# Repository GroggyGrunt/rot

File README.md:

# rot - synthcircuits
easygoing eurorack-modules 

## takt - devided trigger generator

#### takt-ex - expander 

## rør - active multiple

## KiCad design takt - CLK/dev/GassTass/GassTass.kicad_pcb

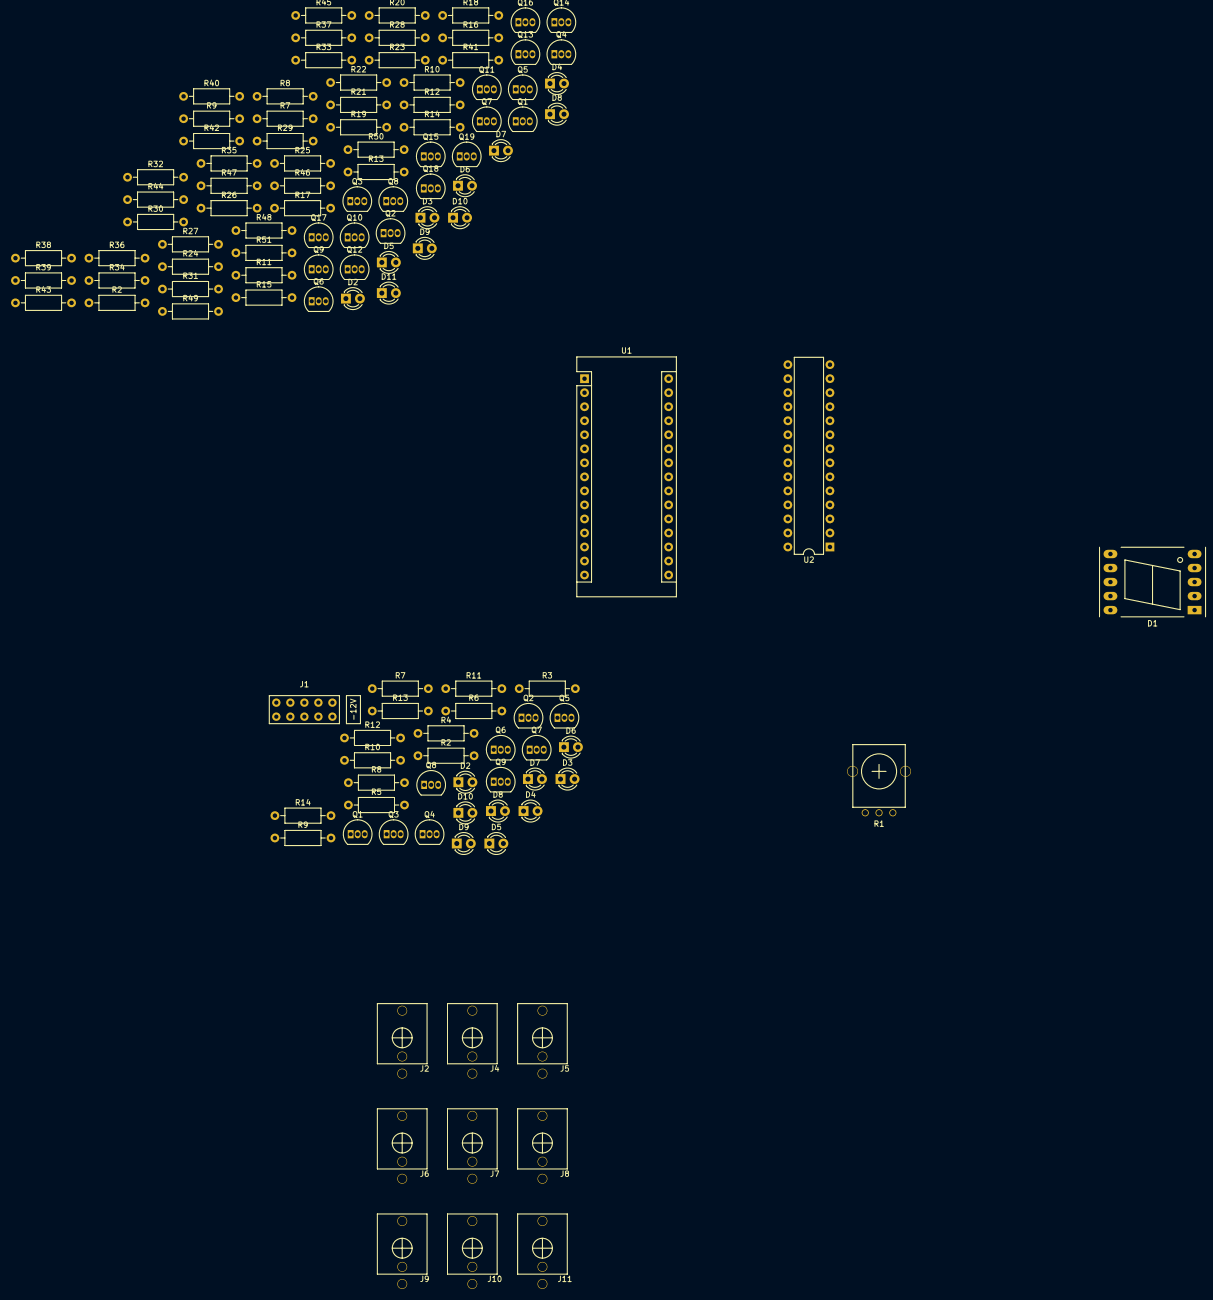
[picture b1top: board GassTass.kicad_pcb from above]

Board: 2 copper layers, 120 parts (0 on the bottom side), 87 nets, no tracks yet.

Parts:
D1: CC56-12CGKWA; 7SegmentLED_LTS6760_LTS6780
D2, D2#2, D3, D3#2, D4, D4#2, D5, D5#2, D6, D6#2, D7, D7#2, D8, D8#2, D9, D9#2, D10, D10#2, D11: LED; LED_D3.0mm_FlatTop
J1: EURO_PWR_2x5; europwr2x5
J2, J4, J5, J6, J7, J8, J9, J10, J11: PJ301M-12
Q1, Q1#2, Q2, Q2#2, Q3, Q3#2, Q4, Q4#2, Q5, Q5#2, Q6, Q6#2, Q7, Q7#2, Q8, Q8#2, Q9, Q9#2, Q10, Q11, Q12, Q13, Q14, Q15, Q16, Q17, Q18, Q19: 2N3904; TO-92_Inline
R1: R_POT_US; Alpha9mmPot
R2, R11, R17, R22, R27, R32, R37, R42, R47: 200; R_Axial_DIN0207_L6.3mm_D2.5mm_P10.16mm_Horizontal
R2#2, R3, R4, R5, R6, R7#2, R8#2, R9#2, R10#2, R11#2, R12#2, R13, R13#2, R14#2: R_US; R_Axial_DIN0207_L6.3mm_D2.5mm_P10.16mm_Horizontal
R7, R9, R10, R12, R15, R16, R18, R20, R21, R23, R25, R26, R28, R30, R31, R33, R35, R36, R38, R40, R41, R43, R45, R46, R48, R50, R51: 1k; R_Axial_DIN0207_L6.3mm_D2.5mm_P10.16mm_Horizontal
R8, R14, R19, R24, R29, R34, R39, R44, R49: 10k; R_Axial_DIN0207_L6.3mm_D2.5mm_P10.16mm_Horizontal
U1: Arduino_Nano_v3.x; Arduino_Nano
U2: ATmega328P-PU; DIP-28_W7.62mm

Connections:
+5V: R8.1, R14.1, R19.1, R24.1, R29.1, R34.1, R39.1, R44.1, R49.1
+12V: J1.1, J1.2, Q1#2.3, Q2#2.3, Q3#2.3, Q4#2.3, Q5.3, Q5#2.3, Q6#2.3, Q7#2.3, Q8#2.3, Q9#2.3, R10.1, R16.1, R21.1, R26.1, R31.1, R36.1, R41.1, R46.1, R51.1
-12V: J1.9, J1.10
GND: D2.1, D3.1, D5.1, D6.1, D7.1, D8.1, D9.1, D10.1, D11.1, J1.3, J1.4, J1.5, J1.6, J1.7, J1.8, J2.1, J2.2, J4.1, J4.2, J5.1, J5.2, J6.1, J6.2, J7.1, J7.2, J8.1, J8.2, J9.1, J9.2, J10.1, J10.2, J11.1, J11.2, Q1.1, Q2.1, Q3.1, Q4.1, Q6.1, Q7.1, Q8.1, Q9.1, Q10.1, Q11.1, Q12.1, Q13.1, Q14.1, Q15.1, Q16.1, Q17.1, Q18.1, Q19.1, R1.1, R2#2.1, R7#2.1, R8#2.1, R9#2.1, R10#2.1, R11#2.1, R12#2.1, R13.1, R13#2.1, R14#2.1, U1.4, U1.29, U2.8, U2.22
unnamed: D1.1, U2.16
unnamed: D1.2, U2.15
unnamed: D1.4, U2.14
unnamed: D1.5, U2.18
unnamed: D1.6, R3.1
unnamed: D1.7, U2.13
unnamed: D1.8, R4.1
unnamed: D1.9, R5.1
unnamed: D1.10, U2.17
unnamed: D2#2.1, R2#2.2
unnamed: D2.2, D2#2.2, Q1#2.2, R2.2
unnamed: D3#2.1, R7#2.2
unnamed: D3.2, D3#2.2, Q2#2.2, R11.2
unnamed: D4.1, D4#2.1, R8#2.2, R13.2
unnamed: D4.2, D4#2.2, Q3#2.2, Q5.2
unnamed: D5#2.1, R9#2.2
unnamed: D5.2, D5#2.2, Q4#2.2, R17.2
unnamed: D6#2.1, R10#2.2
unnamed: D6.2, D6#2.2, Q5#2.2, R22.2
unnamed: D7#2.1, R11#2.2
unnamed: D7.2, D7#2.2, Q6#2.2, R27.2
unnamed: D8#2.1, R12#2.2
unnamed: D8.2, D8#2.2, Q7#2.2, R32.2
unnamed: D9#2.1, R13#2.2
unnamed: D9.2, D9#2.2, Q8#2.2, R37.2
unnamed: D10#2.1, R14#2.2
unnamed: D10.2, D10#2.2, Q9#2.2, R42.2
unnamed: D11.2, R47.2
unnamed: J2.3, Q1#2.1, Q2.3, R10.2
unnamed: Q2#2.1, Q5.1
unnamed: J4.3, Q3#2.1, Q4.3, R16.2
unnamed: J5.3, Q4#2.1, Q7.3, R21.2
unnamed: J6.3, Q5#2.1, Q9.3, R26.2
unnamed: J7.3, Q6#2.1, Q11.3, R31.2
unnamed: J8.3, Q7#2.1, Q13.3, R36.2
unnamed: J9.3, Q8#2.1, Q15.3, R41.2
unnamed: J10.3, Q9#2.1, Q17.3, R46.2
unnamed: J11.3, Q19.3, R51.2
unnamed: Q1.2, R7.2
unnamed: Q1.3, R8.2, R9.2
unnamed: Q2.2, R9.1
unnamed: Q3.2, R12.2
unnamed: Q3.3, R14.2, R15.2
unnamed: Q4.2, R15.1
unnamed: Q6.2, R18.2
unnamed: Q6.3, R19.2, R20.2
unnamed: Q7.2, R20.1
unnamed: Q8.2, R23.2
unnamed: Q8.3, R24.2, R25.2
unnamed: Q9.2, R25.1
unnamed: Q10.2, R28.2
unnamed: Q10.3, R29.2, R30.2
unnamed: Q11.2, R30.1
unnamed: Q12.2, R33.2
unnamed: Q12.3, R34.2, R35.2
unnamed: Q13.2, R35.1
unnamed: Q14.2, R38.2
unnamed: Q14.3, R39.2, R40.2
unnamed: Q15.2, R40.1
unnamed: Q16.2, R43.2
unnamed: Q16.3, R44.2, R45.2
unnamed: Q17.2, R45.1
unnamed: Q18.2, R48.2
unnamed: Q18.3, R49.2, R50.2
unnamed: Q19.2, R50.1
unnamed: R1.2, U1.19
unnamed: R1.3, U1.18
unnamed: R3.2, U2.4
unnamed: R4.2, U2.5
unnamed: R5.2, U2.6
unnamed: R6.2, U2.11
unnamed: U1.23, U2.27
unnamed: U1.24, U2.28
unnamed: U1.27, U2.7
Tr1-in: R2.1, R7.1, U1.5
Tr2-in: R11.1, R12.1, U1.6
Tr3-in: R17.1, R18.1, U1.7
Tr4-in: R22.1, R23.1, U1.8
Tr5-in: R27.1, R28.1, U1.9
Tr6-in: R32.1, R33.1, U1.10
Tr7-in: R37.1, R38.1, U1.11
Tr8-in: R42.1, R43.1, U1.12
Tr9-in: R47.1, R48.1, U1.13

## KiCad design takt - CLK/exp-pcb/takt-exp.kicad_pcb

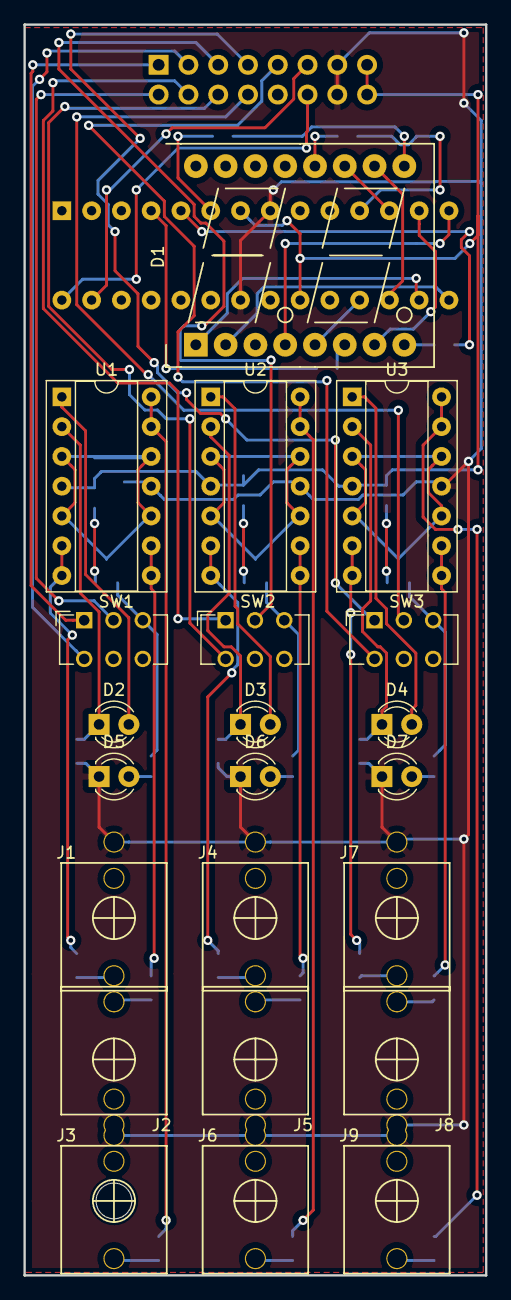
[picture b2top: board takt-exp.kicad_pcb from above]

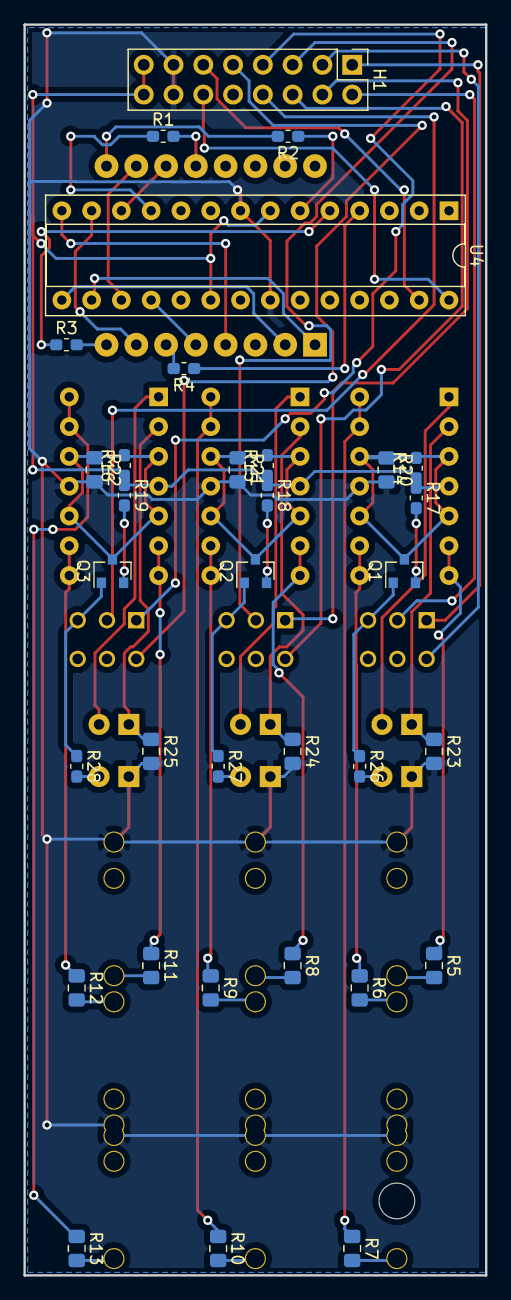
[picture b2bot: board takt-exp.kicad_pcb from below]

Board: 2 copper layers, 39.4 x 106.7 mm, 55 parts (33 on the bottom side), 64 nets.

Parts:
D1: CC56-12CGKWA; AFF_2x7SEG-DIGIT_10mm
D2, D3, D4, D5, D6, D7: LED; LED_D3.0mm_FlatTop
H1: Expander; PinHeader_2x08_P2.54mm_Vertical
J1, J2, J3, J4, J5, J6, J7, J8, J9: PJ301M-12
Q1, Q2, Q3: 2N3904; SOT-23
R1, R2, R3, R4, R26, R27, R28: 200; R_0603_1608Metric_Pad1.05x0.95mm_HandSolder
R5, R6, R7, R8, R9, R10, R11, R12, R13: 51; R_0805_2012Metric_Pad1.15x1.40mm_HandSolder
R14, R15, R16: 6.8k; R_0603_1608Metric_Pad1.05x0.95mm_HandSolder
R17, R18, R19: 2.2k; R_0603_1608Metric_Pad1.05x0.95mm_HandSolder
R20, R21, R22: 10m; R_0805_2012Metric_Pad1.15x1.40mm_HandSolder
R23, R24, R25: 1k; R_0805_2012Metric_Pad1.15x1.40mm_HandSolder
SW1, SW2, SW3: SW_SP3T; SW_CuK_JS202011CQN_DPDT_Straight
U1, U2, U3: TL074; DIP-14_W7.62mm_Socket
U4: ATmega328P-PU; DIP-28_W7.62mm_Socket

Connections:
5V: H1.15, H1.16, R14.1, R15.1, R16.1, R17.1, R18.1, R19.1, U1.4, U2.4, U3.4, U4.7, U4.20
C1: R1.1, U4.11
C2: R2.1, U4.6
C3: R3.1, U4.5
C4: R4.1, U4.4
GND: D5.1, D6.1, D7.1, H1.13, H1.14, J1.1, J2.1, J3.1, J4.1, J5.1, J6.1, J7.1, J8.1, J9.1, R20.2, R21.2, R22.2, R23.2, R24.2, R25.2, U1.11, U2.11, U3.11, U4.8, U4.22
La: D1.11, U4.12
Lb: D1.7, U4.13
Lc: D1.4, U4.14
Ld: D1.2, U4.15
Le: D1.1, U4.16
Lf: D1.10, U4.17
Lg: D1.5, U4.18
unnamed: D1.6, R4.2
unnamed: D1.8, R3.2
unnamed: D1.9, R2.2
unnamed: D1.12, R1.2
unnamed: D2.1, R23.1, U1.2
unnamed: D2.2, U1.1
unnamed: D3.1, R24.1, U2.2
unnamed: D3.2, U2.1
unnamed: D4.1, R25.1, U3.2
unnamed: D4.2, U3.1
unnamed: D5.2, R26.2
unnamed: D6.2, R27.2
unnamed: D7.2, R28.2
unnamed: J1.3, R5.2
unnamed: J2.3, R6.2
unnamed: J3.3, R7.2
unnamed: J4.3, R8.2
unnamed: J5.3, R9.2
unnamed: J6.3, R10.2
unnamed: J7.3, R11.2
unnamed: J8.3, R12.2
unnamed: J9.3, R13.2
unnamed: Q1.2, R17.2
unnamed: Q1.3, R14.2, R20.1, U1.3, U1.5, U1.10, U1.12
unnamed: Q2.2, R18.2
unnamed: Q2.3, R15.2, R21.1, U2.3, U2.5, U2.10, U2.12
unnamed: Q3.2, R19.2
unnamed: Q3.3, R16.2, R22.1, U3.3, U3.5, U3.10, U3.12
unnamed: R5.1, U1.6, U1.7
unnamed: R6.1, U1.8, U1.9
unnamed: R7.1, U1.13, U1.14
unnamed: R8.1, U2.6, U2.7
unnamed: R9.1, U2.8, U2.9
unnamed: R10.1, U2.13, U2.14
unnamed: R11.1, U3.6, U3.7
unnamed: R12.1, U3.8, U3.9
unnamed: R13.1, U3.13, U3.14
SDA: H1.11, U4.27
SDC: H1.12, U4.28
Tr1: H1.1, SW1.1
Tr2: H1.2, SW1.2
Tr3: H1.3, SW1.4
Tr4: H1.4, SW2.1
Tr5: H1.5, SW2.2
Tr6: H1.6, SW2.4
Tr7: H1.7, SW3.1
Tr8: H1.8, SW3.2
Tr9: H1.9, SW3.4
sw1: Q1.1, R26.1, SW1.3
sw2: Q2.1, R27.1, SW2.3
sw3: Q3.1, R28.1, SW3.3

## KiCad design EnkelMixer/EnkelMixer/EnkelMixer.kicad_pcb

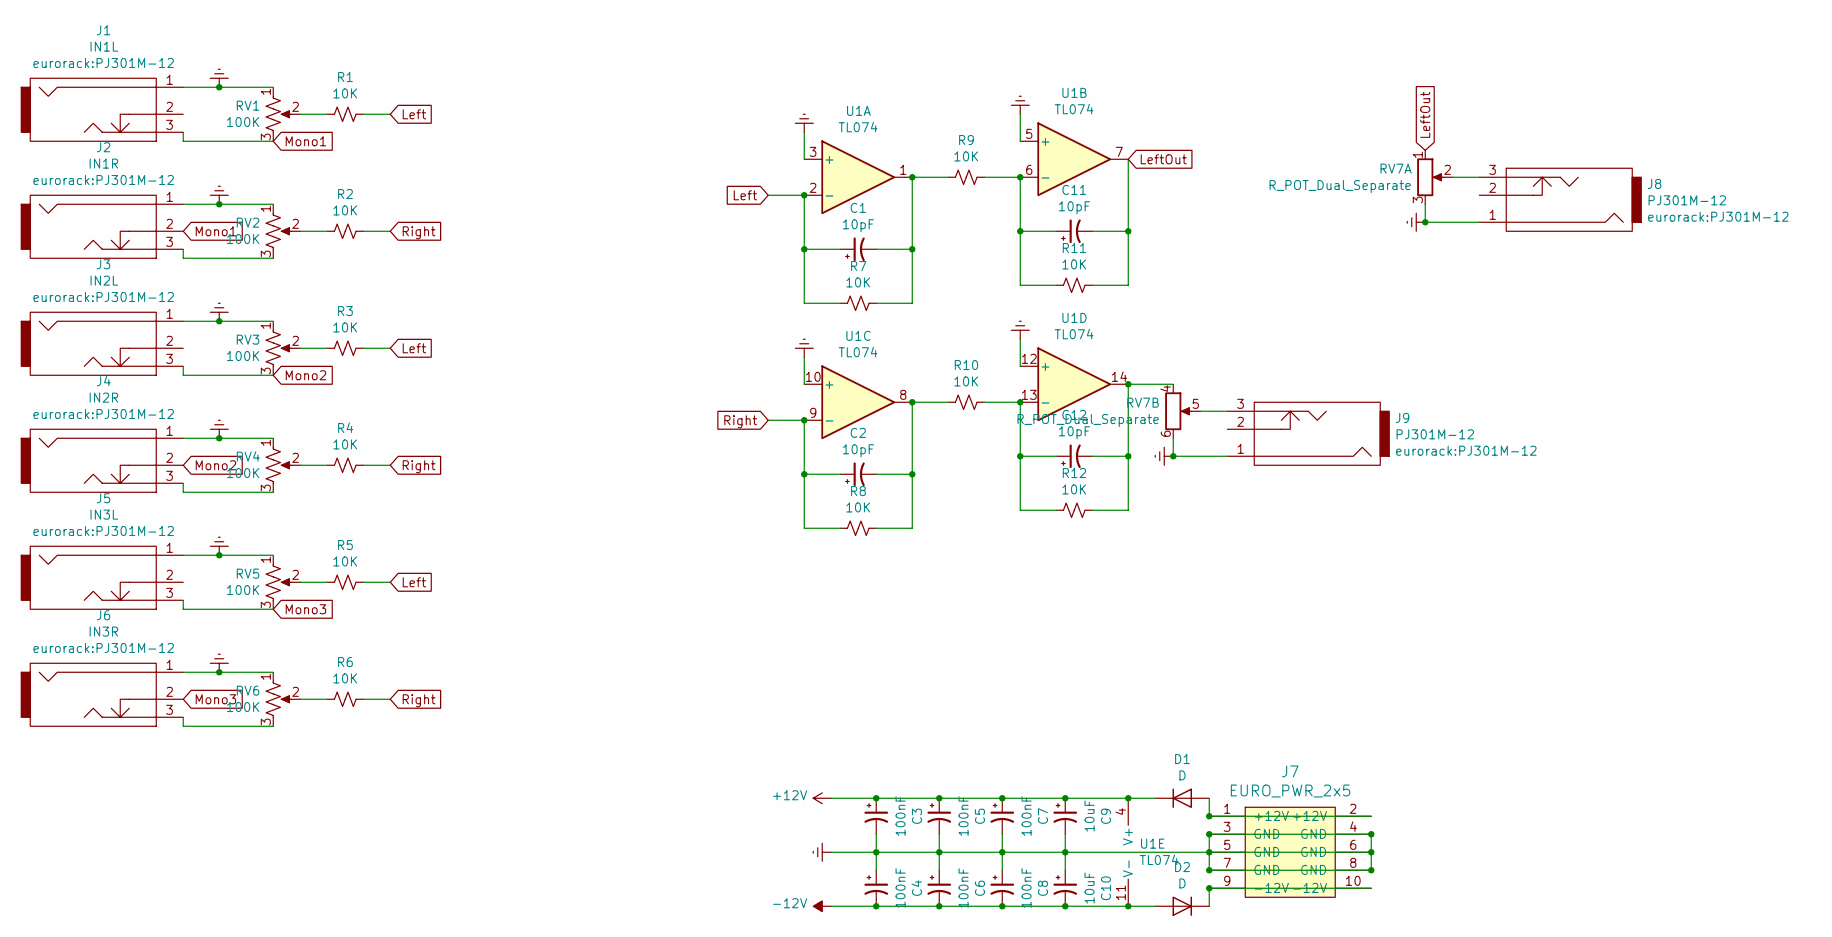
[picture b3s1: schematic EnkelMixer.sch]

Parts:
C1, C2, C11, C12: 10pF; C_Disc_D5.0mm_W2.5mm_P5.00mm
C3, C4, C5, C6, C7, C8: 100nF; C_Disc_D5.0mm_W2.5mm_P5.00mm
C9, C10: 10uF; C_Disc_D5.0mm_W2.5mm_P5.00mm
D1, D2: D; D_A-405_P7.62mm_Horizontal
J1: IN1L; PJ301M-12
J2: IN1R; PJ301M-12
J3: IN2L; PJ301M-12
J4: IN2R; PJ301M-12
J5: IN3L; PJ301M-12
J6: IN3R; PJ301M-12
J7: EURO_PWR_2x5; PinHeader_2x05_P2.54mm_Vertical
J8, J9: PJ301M-12
R1, R2, R3, R4, R5, R6, R7, R8, R9, R10, R11, R12: 10K; R_Axial_DIN0207_L6.3mm_D2.5mm_P5.08mm_Vertical
RV1, RV2, RV3, RV4, RV5, RV6: 100K; Potentiometer_Alpha_RD901F-40-00D_Single_Vertical
RV7: R_POT_Dual_Separate; Potentiometer_Alpha_RD902F-40-00D_Dual_Vertical
U1: TL074; DIP-14_W7.62mm_LongPads

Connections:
+12V: C3.1, C5.1, C7.1, C9.1, D1.1 (K), U1.4 (V+)
-12V: C4.2, C6.2, C8.2, C10.2, D2.2 (A), U1.11 (V-)
Earth: C3.2, C4.1, C5.2, C6.1, C7.2, C8.1, C9.2, C10.1, J1.1, J2.1, J3.1, J4.1, J5.1, J6.1, J7.3 (GND), J7.4 (GND), J7.5 (GND), J7.6 (GND), J7.7 (GND), J7.8 (GND), J8.1, J9.1, RV1.1, RV2.1, RV3.1, RV4.1, RV5.1, RV6.1, RV7.3, RV7.6, U1.3 (+), U1.5 (+), U1.10 (+), U1.12 (+)
Left: C1.1, R1.1, R3.1, R5.1, R7.2, U1.2 (-)
Mono1: J1.3, J2.2, RV1.3
Mono2: J3.3, J4.2, RV3.3
Mono3: J5.3, J6.2, RV5.3
unnamed: C1.2, R7.1, R9.2, U1.1
unnamed: C2.2, R8.1, R10.2, U1.8
unnamed: C11.1, R9.1, R11.2, U1.6 (-)
unnamed: C11.2, R11.1, RV7.1, U1.7
unnamed: C12.1, R10.1, R12.2, U1.13 (-)
unnamed: C12.2, R12.1, RV7.4, U1.14
unnamed: D1.2 (A), J7.1 (+12V), J7.2 (+12V)
unnamed: D2.1 (K), J7.9 (-12V), J7.10 (-12V)
unnamed: J2.3, RV2.3
unnamed: J4.3, RV4.3
unnamed: J6.3, RV6.3
unnamed: J8.3, RV7.2
unnamed: J9.3, RV7.5
unnamed: R1.2, RV1.2
unnamed: R2.2, RV2.2
unnamed: R3.2, RV3.2
unnamed: R4.2, RV4.2
unnamed: R5.2, RV5.2
unnamed: R6.2, RV6.2
Right: C2.1, R2.1, R4.1, R6.1, R8.2, U1.9 (-)

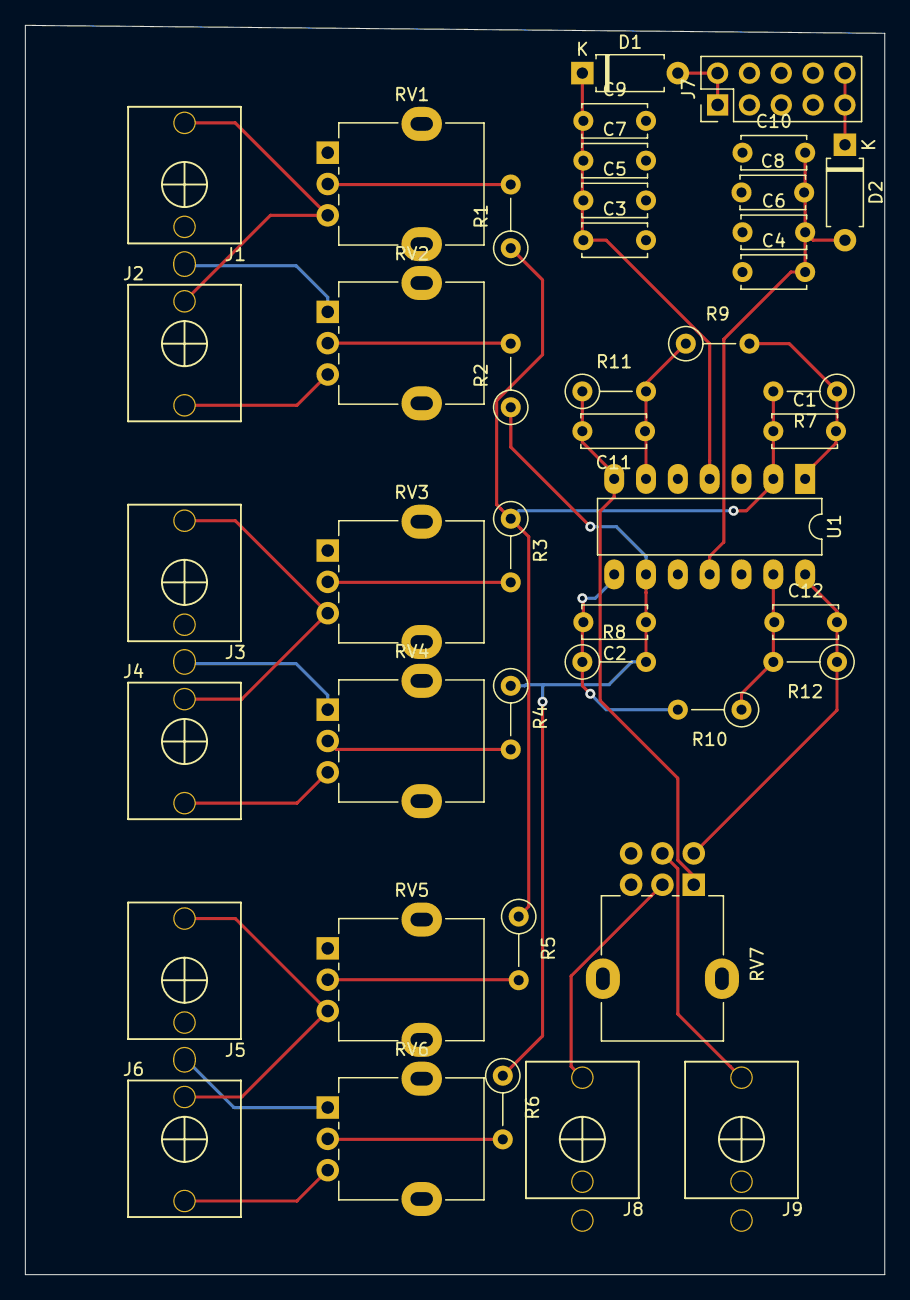
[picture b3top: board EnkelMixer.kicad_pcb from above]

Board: 2 copper layers, 68.6 x 99.7 mm, 43 parts (0 on the bottom side), 27 nets.

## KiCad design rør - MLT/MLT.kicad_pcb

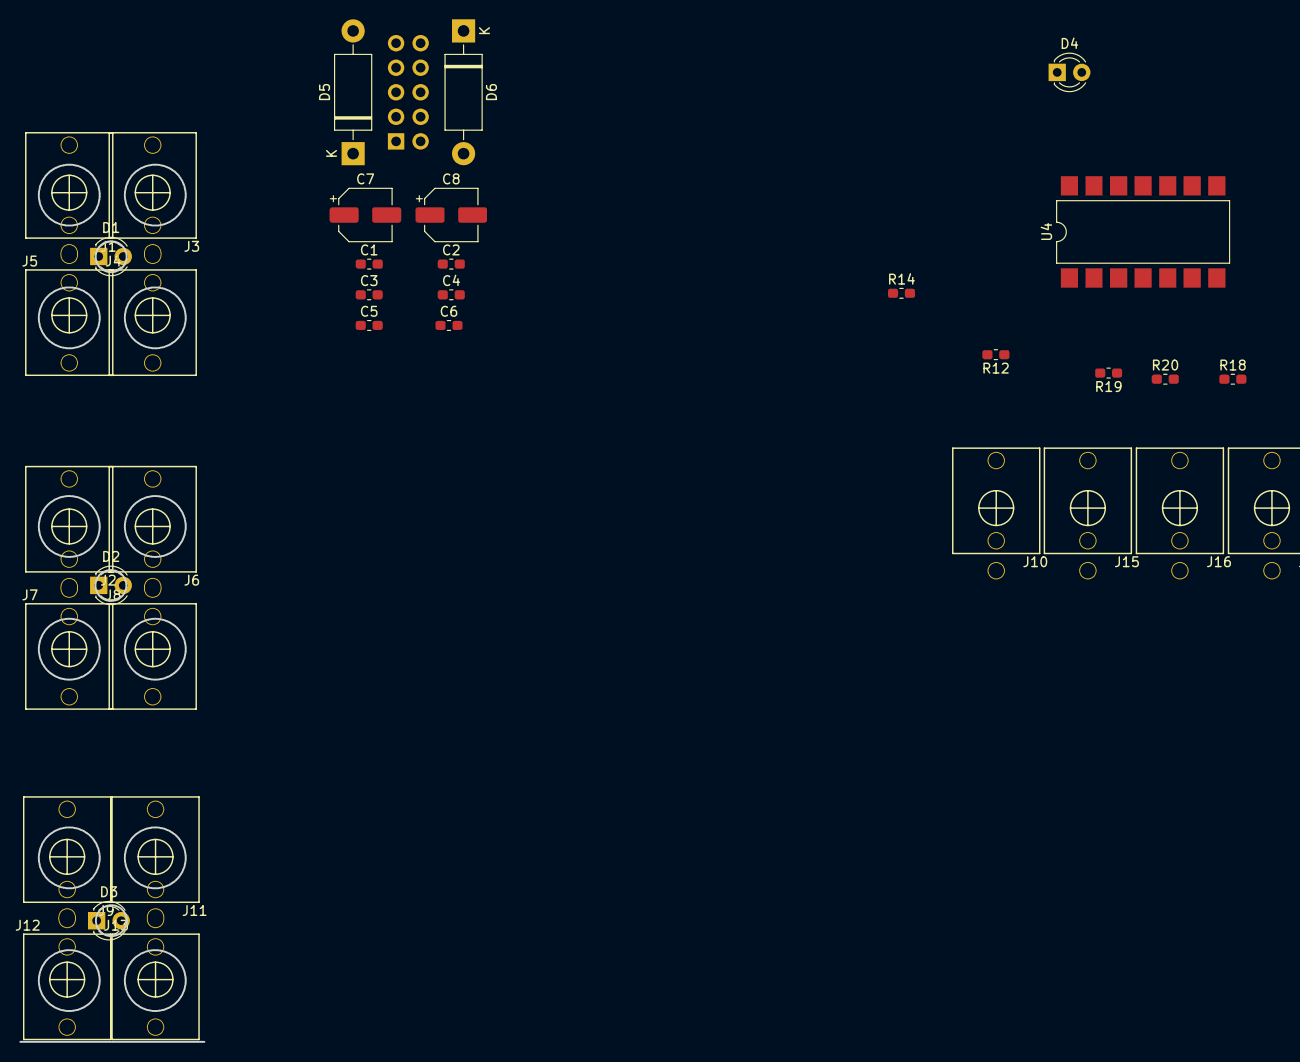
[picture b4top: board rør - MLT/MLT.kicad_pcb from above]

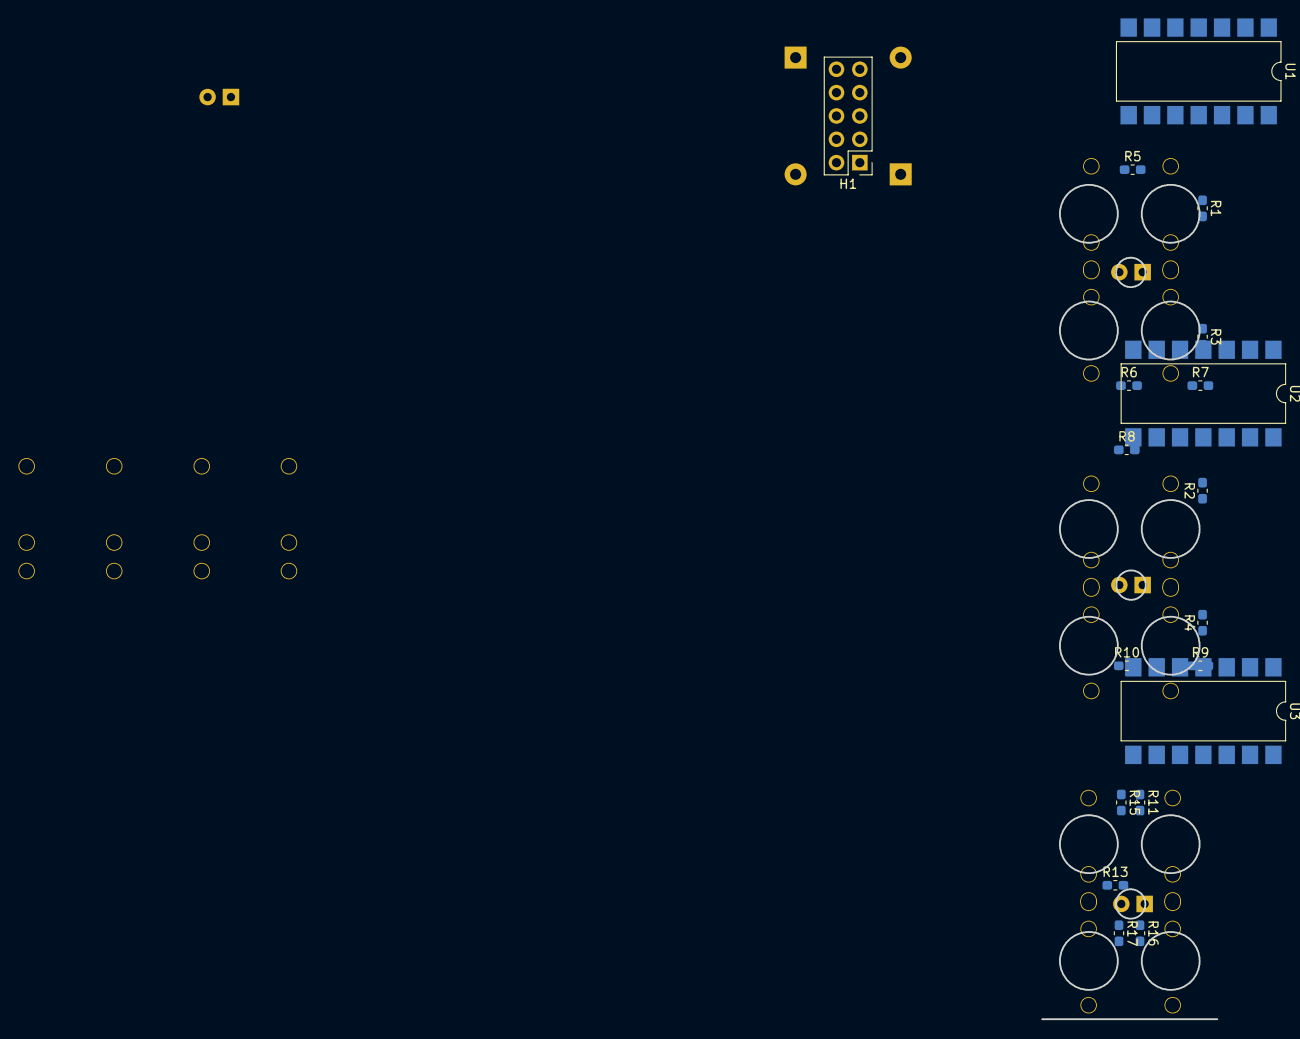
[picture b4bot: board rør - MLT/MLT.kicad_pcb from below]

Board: 2 copper layers, 55 parts (19 on the bottom side), 41 nets, no tracks yet.

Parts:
C1, C2, C3, C4, C5, C6: 100n; C_0603_1608Metric_Pad1.05x0.95mm_HandSolder
C7, C8: 1.7u; CP_Elec_5x5.3
D1, D2, D3, D4: LED; LED_D3.0mm_FlatTop
D5, D6: D; D_DO-15_P12.70mm_Horizontal
H1: PIN_HEADER_2x5; PinHeader_2x05_P2.54mm_Vertical
J1, J2, J3, J4, J5, J6, J7, J8, J9, J10, J11, J12, J13, J14, J15, J16: PJ301M-12
R1, R2, R11, R12: 10m; R_0603_1608Metric_Pad1.05x0.95mm_HandSolder
R3, R4, R13, R14: 1k; R_0603_1608Metric_Pad1.05x0.95mm_HandSolder
R5, R6, R7, R8, R9, R10, R15, R16, R17, R18, R19, R20: 51; R_0603_1608Metric_Pad1.05x0.95mm_HandSolder
U1, U2, U3, U4: TL074; SMDIP-14_W9.53mm

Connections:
GND: C1.2, C2.1, C3.2, C4.1, C5.2, C6.1, C7.2, C8.1, H1.3, H1.4, H1.5, H1.6, H1.7, H1.8, J1.1, J1.2, J2.2, J2.3, J3.1, J4.1, J5.1, J6.1, J7.1, J8.1, J9.1, J9.2, J10.1, J10.2, J11.1, J12.1, J13.1, J14.1, J15.1, J16.1, R1.2, R2.2, R3.1, R4.1, R11.2, R12.2, R13.1, R14.1
unnamed: C1.1, C3.1, C5.1, C7.1, D5.1, U1.4, U2.4, U3.4, U4.4
unnamed: C2.2, C4.2, C6.2, C8.2, D6.2, U1.11, U2.11, U3.11, U4.11
unnamed: D1.1, U1.14
unnamed: D1.2, R3.2, U1.13
unnamed: D2.1, U2.14
unnamed: D2.2, R4.2, U2.13
unnamed: D3.1, U3.14
unnamed: D3.2, R13.2, U3.13
unnamed: D4.1, U4.14
unnamed: D4.2, R14.2, U4.13
unnamed: D5.2, H1.1, H1.2
unnamed: D6.1, H1.9, H1.10
unnamed: J1.3, R1.1, U1.3, U1.5, U1.10, U1.12
unnamed: J2.1, R2.1, U2.3, U2.5, U2.10, U2.12
unnamed: J3.3, R5.2
unnamed: J4.3, R6.2
unnamed: J5.3, R7.2
unnamed: J6.3, R8.2
unnamed: J7.3, R9.2
unnamed: J8.3, R10.2
unnamed: J9.3, R11.1, U3.3, U3.5, U3.10, U3.12
unnamed: J10.3, R12.1, U4.3, U4.5, U4.10, U4.12
unnamed: J11.3, R15.2
unnamed: J12.3, R16.2
unnamed: J13.3, R17.2
unnamed: J14.3, R18.2
unnamed: J15.3, R19.2
unnamed: J16.3, R20.2
unnamed: R5.1, U1.1, U1.2
unnamed: R6.1, U1.6, U1.7
unnamed: R7.1, U1.8, U1.9
unnamed: R8.1, U2.1, U2.2
unnamed: R9.1, U2.6, U2.7
unnamed: R10.1, U2.8, U2.9
unnamed: R15.1, U3.1, U3.2
unnamed: R16.1, U3.6, U3.7
unnamed: R17.1, U3.8, U3.9
unnamed: R18.1, U4.1, U4.2
unnamed: R19.1, U4.6, U4.7
unnamed: R20.1, U4.8, U4.9

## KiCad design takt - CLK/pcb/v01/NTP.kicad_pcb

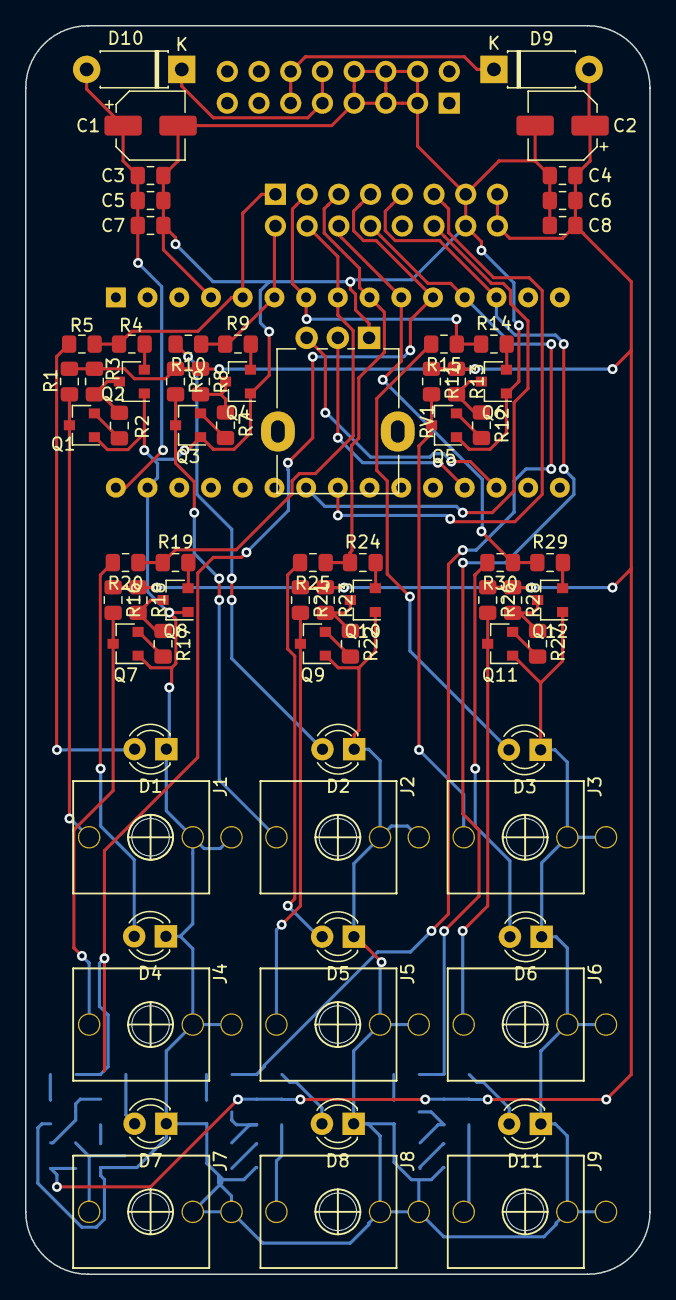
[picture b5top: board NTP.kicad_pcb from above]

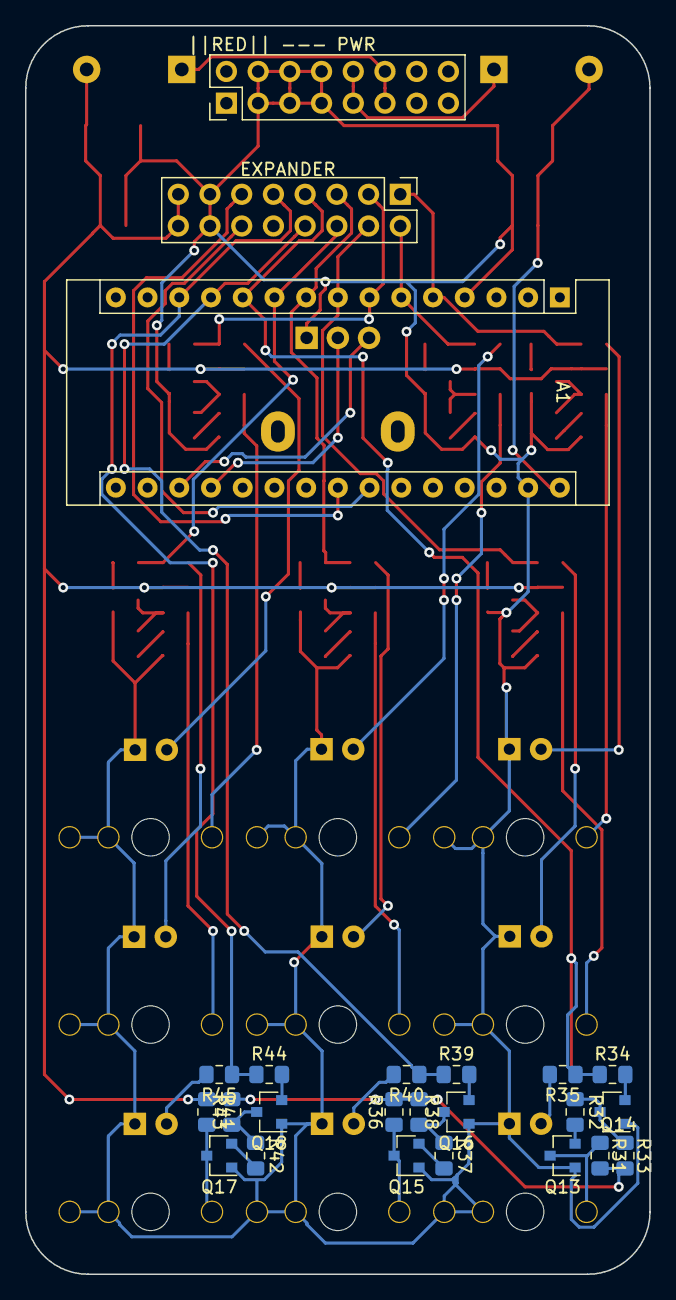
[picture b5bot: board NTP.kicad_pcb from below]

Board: 2 copper layers, 50.0 x 100.0 mm, 95 parts (24 on the bottom side), 63 nets.

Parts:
A1: Arduino_Nano_v3.x; Arduino_Nano
C1, C2: 470n; CP_Elec_5x5.3
C3, C4, C5, C6, C7, C8: 22n; C_0805_2012Metric_Pad1.15x1.40mm_HandSolder
D1, D2, D3, D4, D5, D6, D7, D8, D11: LED; LED_D3.0mm_FlatTop
D9, D10: 1N4006; D_DO-41_SOD81_P7.62mm_Horizontal
EXPANDER: Expander; PinHeader_2x08_P2.54mm_Vertical
J1, J2, J3, J4, J5, J6, J7, J8, J9: PJ301M-12
Q1, Q2, Q3, Q4, Q5, Q6, Q7, Q8, Q9, Q10, Q11, Q12, Q13, Q14, Q15, Q16, Q17, Q18: 2N3904; SOT-23
R1, R2, R4, R6, R7, R9, R11, R12, R14, R16, R17, R19, R21, R22, R24, R26, R27, R29, R31, R32, R34, R36, R37, R39, R41, R42, R44: 1k; R_0805_2012Metric_Pad1.15x1.40mm_HandSolder
R3, R8, R13, R18, R23, R28, R33, R38, R43: 10k; R_0805_2012Metric_Pad1.15x1.40mm_HandSolder
R5, R10, R15, R20, R25, R30, R35, R40, R45: 200; R_0805_2012Metric_Pad1.15x1.40mm_HandSolder
RV1: R_POT_US; Potentiometer_Alpha_RD901F-40-00D_Single_Vertical
||RED|| --- PWR: PIN_HEADER_2x8; PinHeader_2x08_P2.54mm_Vertical

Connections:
5V: C2.1, C4.1, C6.1, C8.1, D9.2, EXPANDER.15, EXPANDER.16, R1.1, R3.1, R6.1, R8.1, R11.1, R13.1, R16.1, R18.1, R21.1, R23.1, R26.1, R28.1, R31.1, R33.1, R36.1, R38.1, R41.1, R43.1
12V: A1.30, C1.1, C3.1, C5.1, C7.1, D10.2
GND: A1.4, A1.29, C1.2, C2.2, C3.2, C4.2, C5.2, C6.2, C7.2, C8.2, D1.1, D2.1, D3.1, D4.1, D5.1, D6.1, D7.1, D8.1, D11.1, EXPANDER.13, EXPANDER.14, J1.1, J1.2, J2.1, J2.2, J3.1, J3.2, J4.1, J4.2, J5.1, J5.2, J6.1, J6.2, J7.1, J7.2, J8.1, J8.2, J9.1, J9.2, Q1.1, Q2.1, Q3.1, Q4.1, Q5.1, Q6.1, Q7.1, Q8.1, Q9.1, Q10.1, Q11.1, Q12.1, Q13.1, Q14.1, Q15.1, Q16.1, Q17.1, Q18.1, RV1.1, ||RED|| --- PWR.3, ||RED|| --- PWR.4, ||RED|| --- PWR.5, ||RED|| --- PWR.6, ||RED|| --- PWR.7, ||RED|| --- PWR.8
unnamed: A1.18, RV1.3
unnamed: A1.19, RV1.2
unnamed: D1.2, R5.2
unnamed: D2.2, R10.2
unnamed: D3.2, R15.2
unnamed: D4.2, R20.2
unnamed: D5.2, R25.2
unnamed: D6.2, R30.2
unnamed: D7.2, R35.2
unnamed: D8.2, R40.2
unnamed: D9.1, ||RED|| --- PWR.11, ||RED|| --- PWR.12
unnamed: D10.1, ||RED|| --- PWR.9, ||RED|| --- PWR.10
unnamed: D11.2, R45.2
unnamed: J1.3, Q1.3, R1.2
unnamed: J2.3, Q3.3, R6.2
unnamed: J3.3, Q5.3, R11.2
unnamed: J4.3, Q7.3, R16.2
unnamed: J5.3, Q9.3, R21.2
unnamed: J6.3, Q11.3, R26.2
unnamed: J7.3, Q13.3, R31.2
unnamed: J8.3, Q15.3, R36.2
unnamed: J9.3, Q17.3, R41.2
unnamed: Q1.2, R2.2
unnamed: Q2.2, R4.2
unnamed: Q2.3, R2.1, R3.2
unnamed: Q3.2, R7.2
unnamed: Q4.2, R9.2
unnamed: Q4.3, R7.1, R8.2
unnamed: Q5.2, R12.2
unnamed: Q6.2, R14.2
unnamed: Q6.3, R12.1, R13.2
unnamed: Q7.2, R17.2
unnamed: Q8.2, R19.2
unnamed: Q8.3, R17.1, R18.2
unnamed: Q9.2, R22.2
unnamed: Q10.2, R24.2
unnamed: Q10.3, R22.1, R23.2
unnamed: Q11.2, R27.2
unnamed: Q12.2, R29.2
unnamed: Q12.3, R27.1, R28.2
unnamed: Q13.2, R32.2
unnamed: Q14.2, R34.2
unnamed: Q14.3, R32.1, R33.2
unnamed: Q15.2, R37.2
unnamed: Q16.2, R39.2
unnamed: Q16.3, R37.1, R38.2
unnamed: Q17.2, R42.2
unnamed: Q18.2, R44.2
unnamed: Q18.3, R42.1, R43.2
SDA: A1.23, EXPANDER.11
SDC: A1.24, EXPANDER.12
Tr1: A1.5, EXPANDER.1, R4.1, R5.1
Tr2: A1.6, EXPANDER.2, R9.1, R10.1
Tr3: A1.7, EXPANDER.3, R14.1, R15.1
Tr4: A1.8, EXPANDER.4, R19.1, R20.1
Tr5: A1.9, EXPANDER.5, R24.1, R25.1
Tr6: A1.10, EXPANDER.6, R29.1, R30.1
Tr7: A1.11, EXPANDER.7, R34.1, R35.1
Tr8: A1.12, EXPANDER.8, R39.1, R40.1
Tr9: A1.13, EXPANDER.9, R44.1, R45.1

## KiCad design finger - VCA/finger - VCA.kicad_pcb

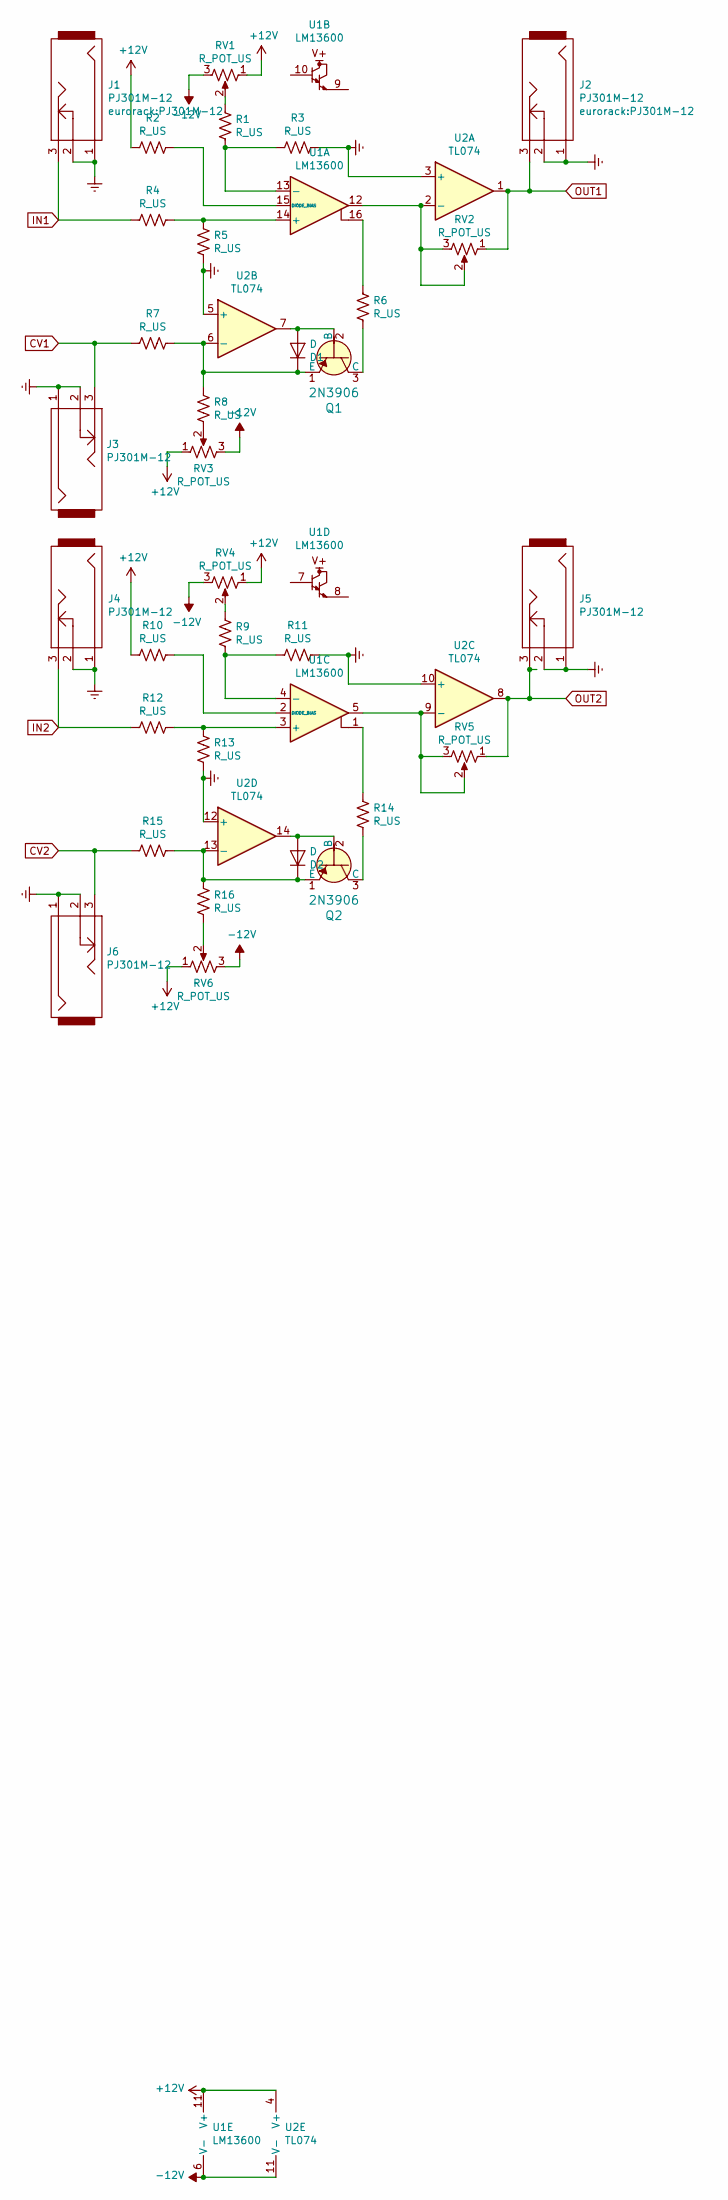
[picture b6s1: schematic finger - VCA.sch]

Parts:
D1, D2: D; D_0603_1608Metric_Pad1.05x0.95mm_HandSolder
J1, J2, J3, J4, J5, J6: PJ301M-12
Q1, Q2: 2N3906; TO-92-3; MPN 2N3906; Digi-Key_PN 2N3906CS-ND
R1, R2, R3, R4, R5, R6, R7, R8, R9, R10, R11, R12, R13, R14, R15, R16: R_US; R_0603_1608Metric_Pad1.05x0.95mm_HandSolder
RV1, RV2, RV3, RV4, RV5, RV6: R_POT_US; Potentiometer_Alpha_RD901F-40-00D_Single_Vertical
U1: LM13600; DIP-16_W7.62mm
U2: TL074; DIP-14_W7.62mm

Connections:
+12V: R2.2, R10.2, RV1.1, RV3.1, RV4.1, RV6.1, U1.11 (V+), U2.4 (V+)
-12V: RV1.3, RV3.3, RV4.3, RV6.3, U1.6 (V-), U2.11 (V-)
CV1: J3.3, R7.2
CV2: J6.3, R15.2
Earth: J1.1, J1.2, J2.1, J2.2, J3.1, J3.2, J4.1, J4.2, J5.1, J5.2, J6.1, J6.2, R3.1, R5.1, R11.1, R13.1, U2.3 (+), U2.5 (+), U2.10 (+), U2.12 (+)
IN1: J1.3, R4.2
IN2: J4.3, R12.2
unnamed: D1.1 (K), Q1.1 (E), R7.1, R8.2, U2.6 (-)
unnamed: D1.2 (A), Q1.2 (B), U2.7
unnamed: D2.1 (K), Q2.1 (E), R15.1, R16.2, U2.13 (-)
unnamed: D2.2 (A), Q2.2 (B), U2.14
unnamed: Q1.3 (C), R6.1
unnamed: Q2.3 (C), R14.1
unnamed: R1.1, R3.2, U1.13 (-)
unnamed: R1.2, RV1.2
unnamed: R2.1, U1.15 (DIODE_BIAS)
unnamed: R4.1, R5.2, U1.14 (+)
unnamed: R6.2, U1.16
unnamed: R8.1, RV3.2
unnamed: R9.2, RV4.2
unnamed: R10.1, U1.2 (DIODE_BIAS)
unnamed: R9.1, R11.2, U1.4 (-)
unnamed: R12.1, R13.2, U1.3 (+)
unnamed: R14.2, U1.1
unnamed: R16.1, RV6.2
unnamed: RV2.2, RV2.3, U1.12, U2.2 (-)
unnamed: RV5.2, RV5.3, U1.5, U2.9 (-)
OUT1: J2.3, RV2.1, U2.1
OUT2: J5.3, RV5.1, U2.8

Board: 2 copper layers, 34 parts (26 on the bottom side), 29 nets, no tracks yet.

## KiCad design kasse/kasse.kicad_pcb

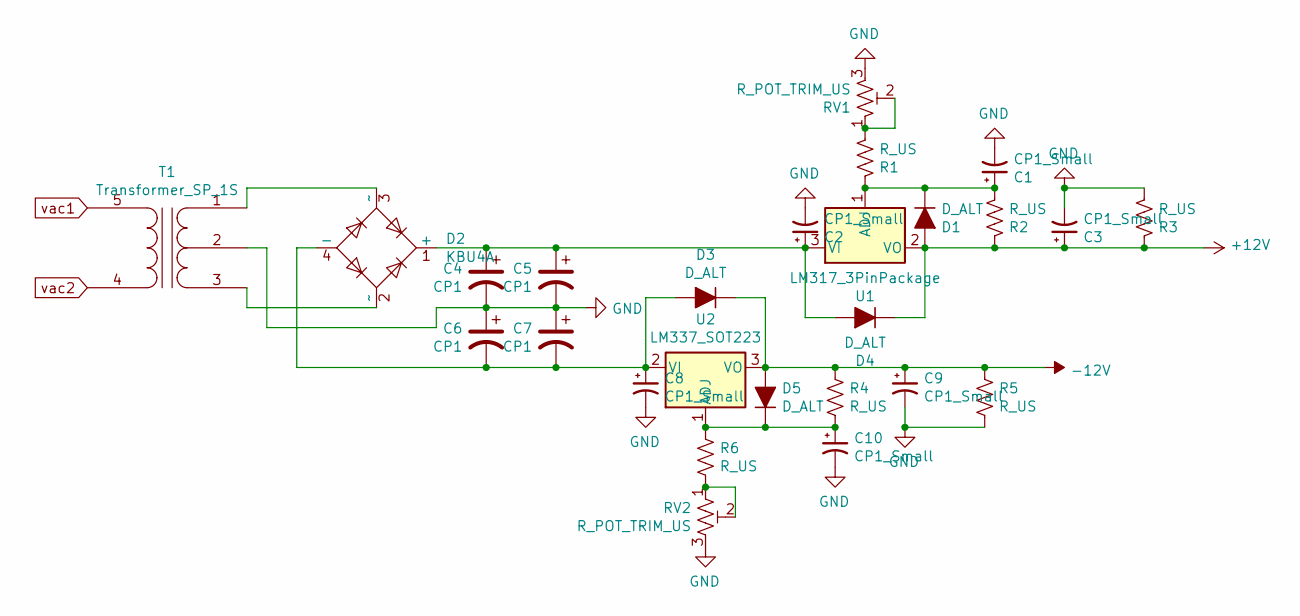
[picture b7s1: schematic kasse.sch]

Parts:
C1, C2, C3, C8, C9, C10: CP1_Small; C_0603_1608Metric_Pad1.05x0.95mm_HandSolder
C4, C5, C6, C7: CP1; CP_Radial_D12.5mm_P5.00mm
D1, D3, D4, D5: D_ALT; D_1206_3216Metric_Pad1.42x1.75mm_HandSolder
D2: KBU4A; Diode_Bridge_Vishay_KBU
R1, R2, R3, R4, R5, R6: R_US; R_0603_1608Metric_Pad1.05x0.95mm_HandSolder
RV1, RV2: R_POT_TRIM_US; Potentiometer_Bourns_3266W_Vertical
T1: Transformer_SP_1S; Transformer_CHK_EI42-5VA_2xSec
U1: LM317_3PinPackage; SOT-223-3_TabPin2
U2: LM337_SOT223; SOT-223-3_TabPin2

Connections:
+12V: C3.1, D1.2 (A), D4.1 (K), R2.1, R3.1, U1.2 (VO)
-12V: C9.1, D3.1 (K), D5.2 (A), R4.1, R5.1, U2.3 (VO)
GND: C1.2, C2.2, C3.2, C4.2, C5.2, C6.1, C7.1, C8.2, C9.2, C10.2, R3.2, R5.2, RV1.3, RV2.3, T1.2 (PM)
unnamed: C1.1, D1.1 (K), R1.1, R2.2, U1.1 (ADJ)
unnamed: C2.1, C4.1, C5.1, D2.1 (+), D4.2 (A), U1.3 (VI)
unnamed: C6.2, C7.2, C8.1, D2.4 (-), D3.2 (A), U2.2 (VI)
unnamed: C10.1, D5.1 (K), R4.2, R6.1, U2.1 (ADJ)
unnamed: D2.2 (~~), T1.3 (PR2)
unnamed: D2.3 (~~), T1.1 (PR1)
unnamed: R1.2, RV1.1, RV1.2
unnamed: R6.2, RV2.1, RV2.2
vac1: T1.5 (S2)
vac2: T1.4 (S1)

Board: 2 copper layers, 26 parts (0 on the bottom side), 11 nets, no tracks yet.
